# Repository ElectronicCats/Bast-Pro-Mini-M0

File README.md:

# Bast Pro Mini M0

**[OSHW] MX0005 | Certified open source hardware |** [oshwa.org/cert.](https://www.oshwa.org/cert)

Electronic Cats Bast are a complete line of development boards for electronic cats.

Bast Pro Mini M0 is all the best in the world Arduino Pro Mini with a SAMD21 M0+ core, 32 bits of power!, Arduino pro mini pin to pin compatible with a micro USB port.

Electronic Cats invests time and resources providing this open source design, please support Electronic Cats and open-source hardware by purchasing products from Electronic Cats!

Designed by Electronic Cats.

## Installation

While the SAMD21 alone is powerful enough, what truly makes it special is its growing support in the Arduino IDE. With just a couple click's, copies, and pastes, you can add ARM Cortex-M0+-support to your Arduino IDE. 

First of all we'll need to install the Arduino SAMD based boards, to do it you just need to go (Tools > Board > Boards Manager...)

And then search for "SAMD"

And install the "Arduino SAMD Board (32-bits ARM Cortex M0+)" once you have installed the Arduino SAMD21 core you must proceed installing our boards variants following the next steps:

Open your Arduino preferences (File > Preferences) or (Arduino > Preferences)

![](https://raw.githubusercontent.com/ElectronicCats/Bast-Pro-Mini-M0/master/docs/images/4_preferences.png
)

You will need to copy the next link into the additional boards manager URL, if you have another link just add a "," before this second link.

`https://electroniccats.github.io/Arduino_Boards_Index/package_electroniccats_index.json
`

Then you can click on the OK button to close the preferences panel and continue the installation.

If you did hit "OK", travel back to the Board Manager menu. You should be able to find a new entry for Electronic Cats. If you don't see it, close the board manager and open it again.

Click on install and once the boards are installed you should be able to select them on the (Tools > Boards) section.

So now you can program your Bast Pro Mini M0 as a common arduino!

Test the Blink example and then start prototyping!  

## Driver for windows 7 and 8.1

[Zadig](https://zadig.akeo.ie/) is the recommended tool to install drivers in Windows. The bootloader (4348,55E0) should be installed with WinUSB or libusb-win32 driver.

You can use USB Serial (CDC) driver for default CDC USB stack. If you tried to emulate another type of USB device without changing the PID/VID, you may need to uninstall the device before installing a new driver.

## Pinout

## License hardware

Hardware released under an CERN Open Hardware Licence v1.2. See the LICENSE_HARDWARE file for more information.

## License Documentation 
<br />Esta obra está bajo una <a rel="license" href="http://creativecommons.org/licenses/by-sa/4.0/">Licencia Creative Commons Atribución-CompartirIgual 4.0 Internacional</a>.

Electronic Cats is a registered trademark, please do not use if you sell these PCBs.

30 Oct 2018

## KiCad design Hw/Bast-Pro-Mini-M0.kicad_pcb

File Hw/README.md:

# Bast Pro Mini M0

**[OSHW] MX0005 | Certified open source hardware |** [oshwa.org/cert.](https://www.oshwa.org/cert)

Electronic Cats Bast are a complete line of development plates for electronic cats.

Bast Pro Mini M0 is all the best in the world Arduino Pro Mini with a core SAMD 21 M0 of 32 bits, pin to pin compatible with a micro USB port

Electronic Cats invests time and resources providing this open source design, please support Electronic Cats and open-source hardware by purchasing products from Electronic Cats!

Designed by Electronic Cats.

## License hardware

Hardware released under an CERN Open Hardware Licence v1.2. See the LICENSE_HARDWARE file for more information.

## License Documentation 
<br />Esta obra está bajo una <a rel="license" href="http://creativecommons.org/licenses/by-sa/4.0/">Licencia Creative Commons Atribución-CompartirIgual 4.0 Internacional</a>.

Electronic Cats is a registered trademark, please do not use if you sell these PCBs.

30 Oct 2018

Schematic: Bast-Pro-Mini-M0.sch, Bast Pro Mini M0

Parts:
C1, C2: 1uF; C_0603_1608Metric_Pad1.05x0.95mm_HandSolder
C3, C4, C5: 0.1uF; C_0603_1608Metric_Pad1.05x0.95mm_HandSolder
D1: POWER; LED_0805_2012Metric_Pad1.15x1.40mm_HandSolder
D2: LED; LED_0805_2012Metric_Pad1.15x1.40mm_HandSolder
F1: 500mA; Fuse_0805_2012Metric_Pad1.15x1.40mm_HandSolder
J1: USB_B_Micro; U254051N4BH806
J2: Conn_02x02_Odd_Even; PinHeader_2x02_P2.54mm_Vertical_SMD
P1: Digital; PinHeader_1x12_P2.54mm_Vertical
P2: ADC; Socket_Strip_Arduino_1x02
P3: Analog; Socket_Strip_Arduino_1x12
R1, R2: 330; R_0603_1608Metric_Pad1.05x0.95mm_HandSolder
SW1: SW_DPST_x2; SW_SPST_TL3342
U1: AP2112K-3.3TRG1; SOT-23-5
U2: ATSAMD21E18A-AF; TQFP-32_7x7mm_P0.8mm

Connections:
+3V3: C2.1, C3.1, C5.1, D1.2, D2.2, J2.1, P3.4, U1.5 (VOUT), U2.9 (VDDANA), U2.30 (VDDIN)
/0(Rx): P1.2, U2.2 (PA01)
/1(Tx): P1.1, U2.1 (PA00)
/2: P1.5, U2.15 (PA14)
/3(**): P1.6, U2.22 (PA23)
/4: P1.7, U2.21 (PA22)
/5(**): P1.8, U2.16 (PA15)
/6(**): P1.9, U2.25 (PA27)
/7: P1.10, U2.27 (PA28)
/8: P1.11, U2.7 (PA06)
/9(**): P1.12, U2.8 (PA07)
/10(**/SS): P3.12, U2.19 (PA18)
/11(**/MOSI): P3.11, U2.17 (PA16)
/12(MISO): P3.10, U2.20 (PA19)
/13(SCK): P3.9, U2.18 (PA17)
/A0: P3.8, U2.3 (PA02)
/A1: P3.7, U2.5 (PA04)
/A2: P3.6, U2.6 (PA05)
/A3: P3.5, U2.13 (PA10)
/D+: J1.3, U2.24 (PA25)
/D-: J1.2, U2.23 (PA24)
/LED: R2.2, U2.14 (PA11)
/RESET: P1.3, P3.3, SW1.1, U2.26 (~RESET~)
/SCL: P2.2, U2.12 (PA09)
/SDA: P2.1, U2.11 (PA08)
/SWCLK: J2.4, U2.31 (PA30)
/SWDIO: J2.3, U2.32 (PA31)
GND: C1.2, C2.2, C3.2, C4.2, C5.2, J1.5, J2.2, P1.4, P3.2, R1.2, SW1.2, U1.2 (GND), U2.10 (GND), U2.28 (GND)
unnamed: C4.1, U2.29 (VDDCORE)
unnamed: D1.1, R1.1
unnamed: D2.1, R2.1
unnamed: F1.2, J1.1
VCC: C1.1, F1.1, P3.1, U1.1 (VIN), U1.3 (EN)

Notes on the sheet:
BAST PRO MINI M0
SAMD21
SOURCE
USB & SWD PORT

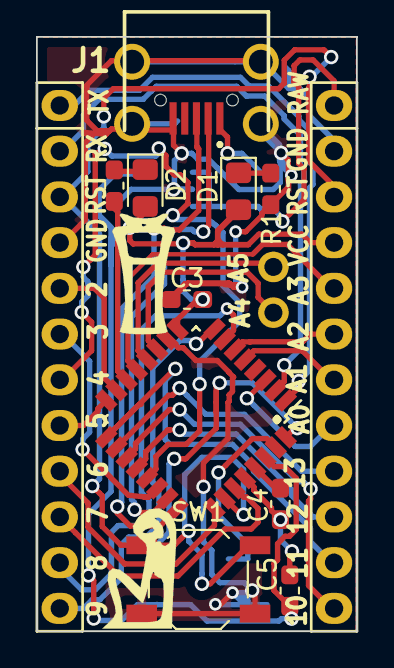
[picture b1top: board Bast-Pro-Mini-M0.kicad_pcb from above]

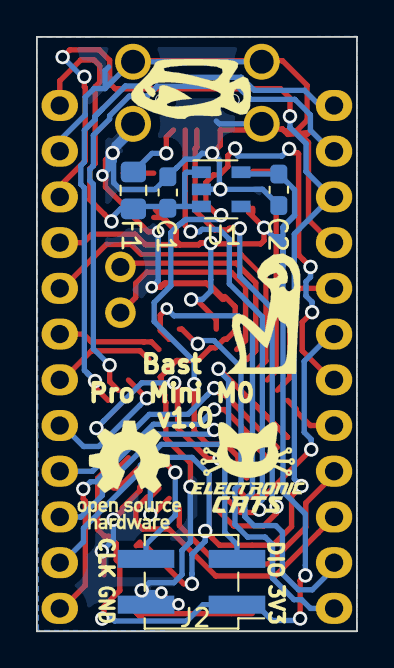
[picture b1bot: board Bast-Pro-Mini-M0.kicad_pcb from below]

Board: 2 copper layers, 17.8 x 33.0 mm, 18 parts (5 on the bottom side), 33 nets.

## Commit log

2018-09-28 Schematic initial
2018-09-28 add extras
2018-09-28 add ignore
2018-09-29 Schematic finished
2018-09-29 Schematic finished, now yes
2018-10-02 first components places
2018-10-02 update gitignore
2018-10-03 Second arrangement of components in pcb
2018-10-04 Add logos
2018-10-07 Remove leds and change pins I2C
2018-10-07 Pre router
2018-10-08 V0.2 Fix Connection
2018-10-10 Dimensions of Bast Pro Mini M0
2018-10-16 added gitgnore
2018-10-16 Add art
2018-10-30 New pcb's Bast
2018-10-30 Rename files Bast Pro Mini M0
2018-10-31 first design
2018-10-31 Bast Pro Mini (ultimate revision)
2018-10-31 Bast Pro Mini (utimate revision) (Now yes)
2018-11-01 Bast Pro Mini M0 add 3d model usb
2018-11-01 Add gebers rules
2018-11-01 silkscreen number pins
2018-11-01 Fix details
2018-11-01 update no changes
2018-11-01 label v0.1 add
2018-11-04 Add hardware license
2018-11-09 bast revision
2018-11-10 Fix tracks and update revision
2018-11-10 Fix vias, add version on board
2018-11-11 Update README documentation CC
2018-11-11 Add image MX0005 OSHW
2018-11-11 Update README OSHW MX0005
2018-11-28 Update tracks
2019-01-10 Add BOM
2019-02-25 bump :)
2019-03-27 MOve hardware to its folder
2019-03-27 add render image
2019-03-27 Move README
2019-03-27 add images for installation
2019-03-27 Add images for installation process
2019-03-27 erase netlist from root
2019-03-28 Change type of button
2019-03-28 fix traces
2019-05-08 Add CircuitPython examples
2019-05-23 Add Circuit Python examples
2019-05-24 add rescue lib emove from gitignore
2019-07-22 Change caps
2019-11-15 Update V1.0 silkscreen
2019-12-02 Add pinout PDF and PNG
2020-01-09 Update pinout
2020-01-13 Add DAC to pinout diagram
2021-03-01 Fix README.md typo
2022-03-28 Update formatting
2022-09-29 Issue template added
